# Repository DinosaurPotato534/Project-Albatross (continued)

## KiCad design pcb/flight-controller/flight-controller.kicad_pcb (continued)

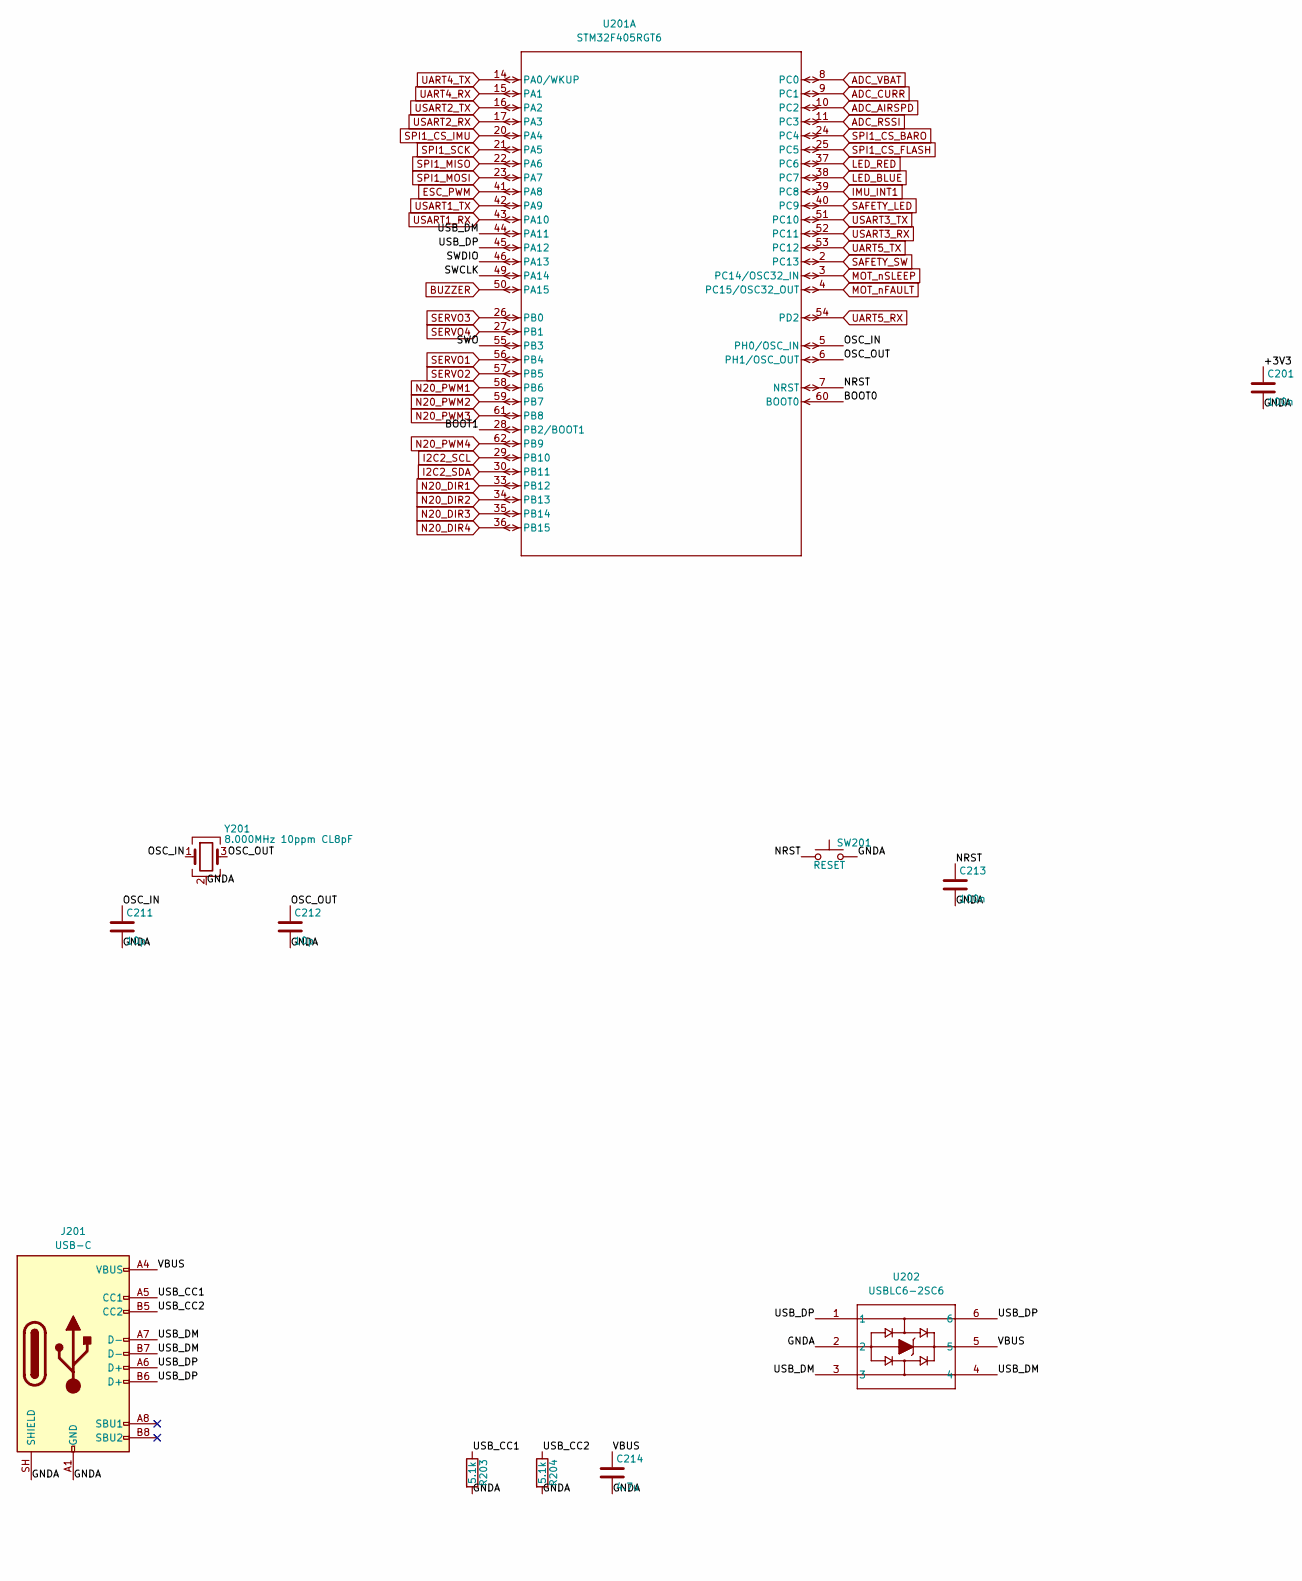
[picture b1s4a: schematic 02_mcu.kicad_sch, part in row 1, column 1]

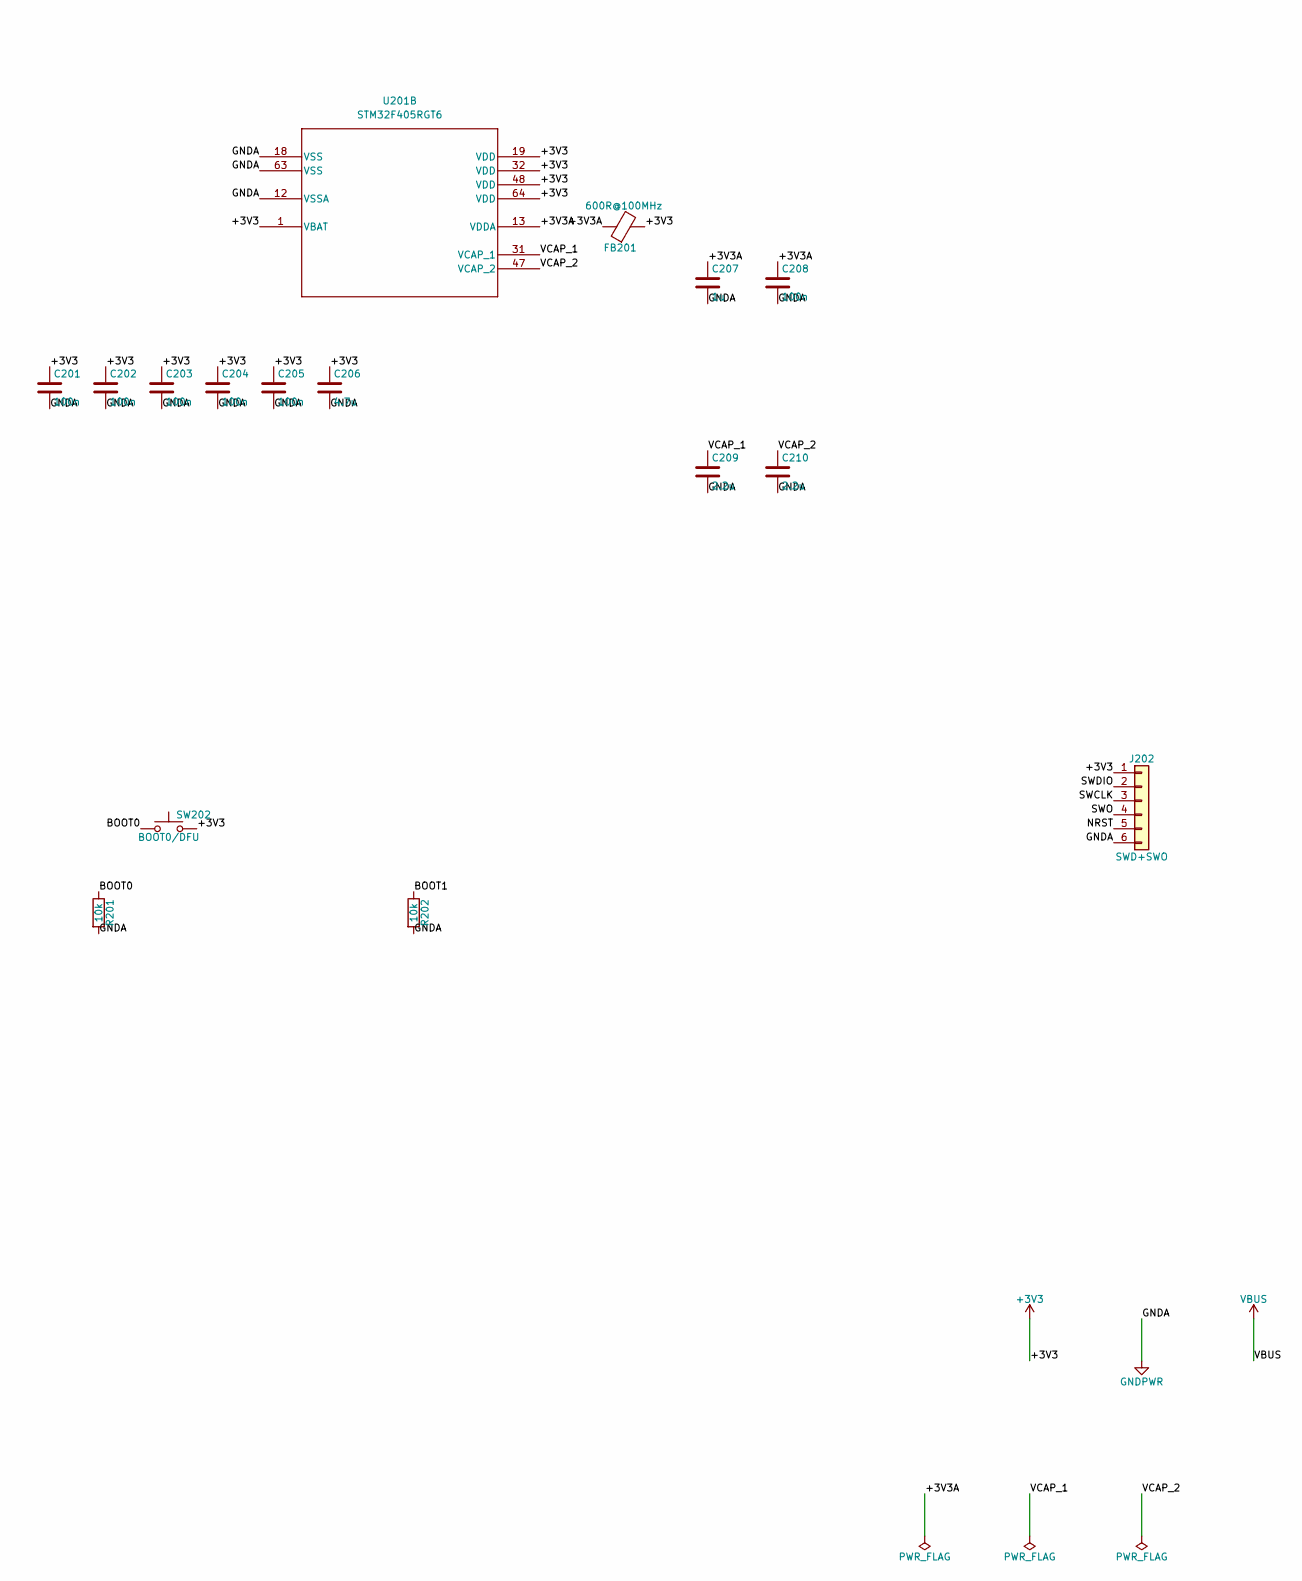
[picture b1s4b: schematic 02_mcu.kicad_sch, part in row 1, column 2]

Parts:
C201, C202, C203, C204, C205, C208, C213: 100n; C_0402_1005Metric
C206, C214: 4.7u; C_0805_2012Metric
C207: 1u; C_0603_1608Metric
C209, C210: 2.2u; C_0603_1608Metric
C211, C212: 10p; C_0402_1005Metric
FB201: 600R@100MHz; L_0805_2012Metric
J201: USB-C; USB_C_Receptacle_GCT_USB4085
J202: SWD+SWO; PinHeader_1x06_P1.27mm_Vertical
R201, R202: 10k; R_0603_1608Metric
R203, R204: 5.1k; R_0402_1005Metric
SW201: RESET; SW_SPST_B3S-1000
SW202: BOOT0/DFU; SW_SPST_B3S-1000
U201: STM32F405RGT6; LQFP64-10x10mm
U202: USBLC6-2SC6; SOT23-6L_STM
Y201: 8.000MHz 10ppm CL8pF; Crystal_SMD_3225-4Pin_3.2x2.5mm

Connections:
/02_MCU/BOOT0: R201.1, SW202.1, U201.60 (BOOT0)
/02_MCU/BOOT1: R202.1, U201.28 (PB2/BOOT1)
/02_MCU/NRST: C213.1, J202.5, SW201.1, U201.7 (NRST)
/02_MCU/OSC_IN: C211.1, U201.5 (PH0/OSC_IN), Y201.1
/02_MCU/OSC_OUT: C212.1, U201.6 (PH1/OSC_OUT), Y201.3
/02_MCU/SWCLK: J202.3, U201.49 (PA14)
/02_MCU/SWDIO: J202.2, U201.46 (PA13)
/02_MCU/SWO: J202.4, U201.55 (PB3)
/02_MCU/USB_CC1: J201.A5 (CC1), R203.1
/02_MCU/USB_CC2: J201.B5 (CC2), R204.1
/02_MCU/USB_DM: J201.A7 (D-), J201.B7 (D-), U201.44 (PA11), U202.3, U202.4
/02_MCU/USB_DP: J201.A6 (D+), J201.B6 (D+), U201.45 (PA12), U202.1, U202.6
ADC_AIRSPD: U201.10 (PC2); also elsewhere on the board
ADC_CURR: U201.9 (PC1); also elsewhere on the board
ADC_RSSI: U201.11 (PC3); also elsewhere on the board
ADC_VBAT: U201.8 (PC0); also elsewhere on the board
BUZZER: U201.50 (PA15); also elsewhere on the board
ESC_PWM: U201.41 (PA8); also elsewhere on the board
I2C2_SCL: U201.29 (PB10); also elsewhere on the board
I2C2_SDA: U201.30 (PB11); also elsewhere on the board
IMU_INT1: U201.39 (PC8); also elsewhere on the board
LED_BLUE: U201.38 (PC7); also elsewhere on the board
LED_RED: U201.37 (PC6); also elsewhere on the board
MOT_nFAULT: U201.4 (PC15/OSC32_OUT); also elsewhere on the board
MOT_nSLEEP: U201.3 (PC14/OSC32_IN); also elsewhere on the board
N20_DIR1: U201.33 (PB12); also elsewhere on the board
N20_DIR2: U201.34 (PB13); also elsewhere on the board
N20_DIR3: U201.35 (PB14); also elsewhere on the board
N20_DIR4: U201.36 (PB15); also elsewhere on the board
N20_PWM1: U201.58 (PB6); also elsewhere on the board
N20_PWM2: U201.59 (PB7); also elsewhere on the board
N20_PWM3: U201.61 (PB8); also elsewhere on the board
N20_PWM4: U201.62 (PB9); also elsewhere on the board
SAFETY_LED: U201.40 (PC9); also elsewhere on the board
SAFETY_SW: U201.2 (PC13); also elsewhere on the board
SERVO1: U201.56 (PB4); also elsewhere on the board
SERVO2: U201.57 (PB5); also elsewhere on the board
SERVO3: U201.26 (PB0); also elsewhere on the board
SERVO4: U201.27 (PB1); also elsewhere on the board
SPI1_CS_BARO: U201.24 (PC4); also elsewhere on the board
SPI1_CS_FLASH: U201.25 (PC5); also elsewhere on the board
SPI1_CS_IMU: U201.20 (PA4); also elsewhere on the board
SPI1_MISO: U201.22 (PA6); also elsewhere on the board
SPI1_MOSI: U201.23 (PA7); also elsewhere on the board
SPI1_SCK: U201.21 (PA5); also elsewhere on the board
UART4_RX: U201.15 (PA1); also elsewhere on the board
UART4_TX: U201.14 (PA0/WKUP); also elsewhere on the board
UART5_RX: U201.54 (PD2); also elsewhere on the board
UART5_TX: U201.53 (PC12); also elsewhere on the board
USART1_RX: U201.43 (PA10); also elsewhere on the board
USART1_TX: U201.42 (PA9); also elsewhere on the board
USART2_RX: U201.17 (PA3); also elsewhere on the board
USART2_TX: U201.16 (PA2); also elsewhere on the board
USART3_RX: U201.52 (PC11); also elsewhere on the board
USART3_TX: U201.51 (PC10); also elsewhere on the board

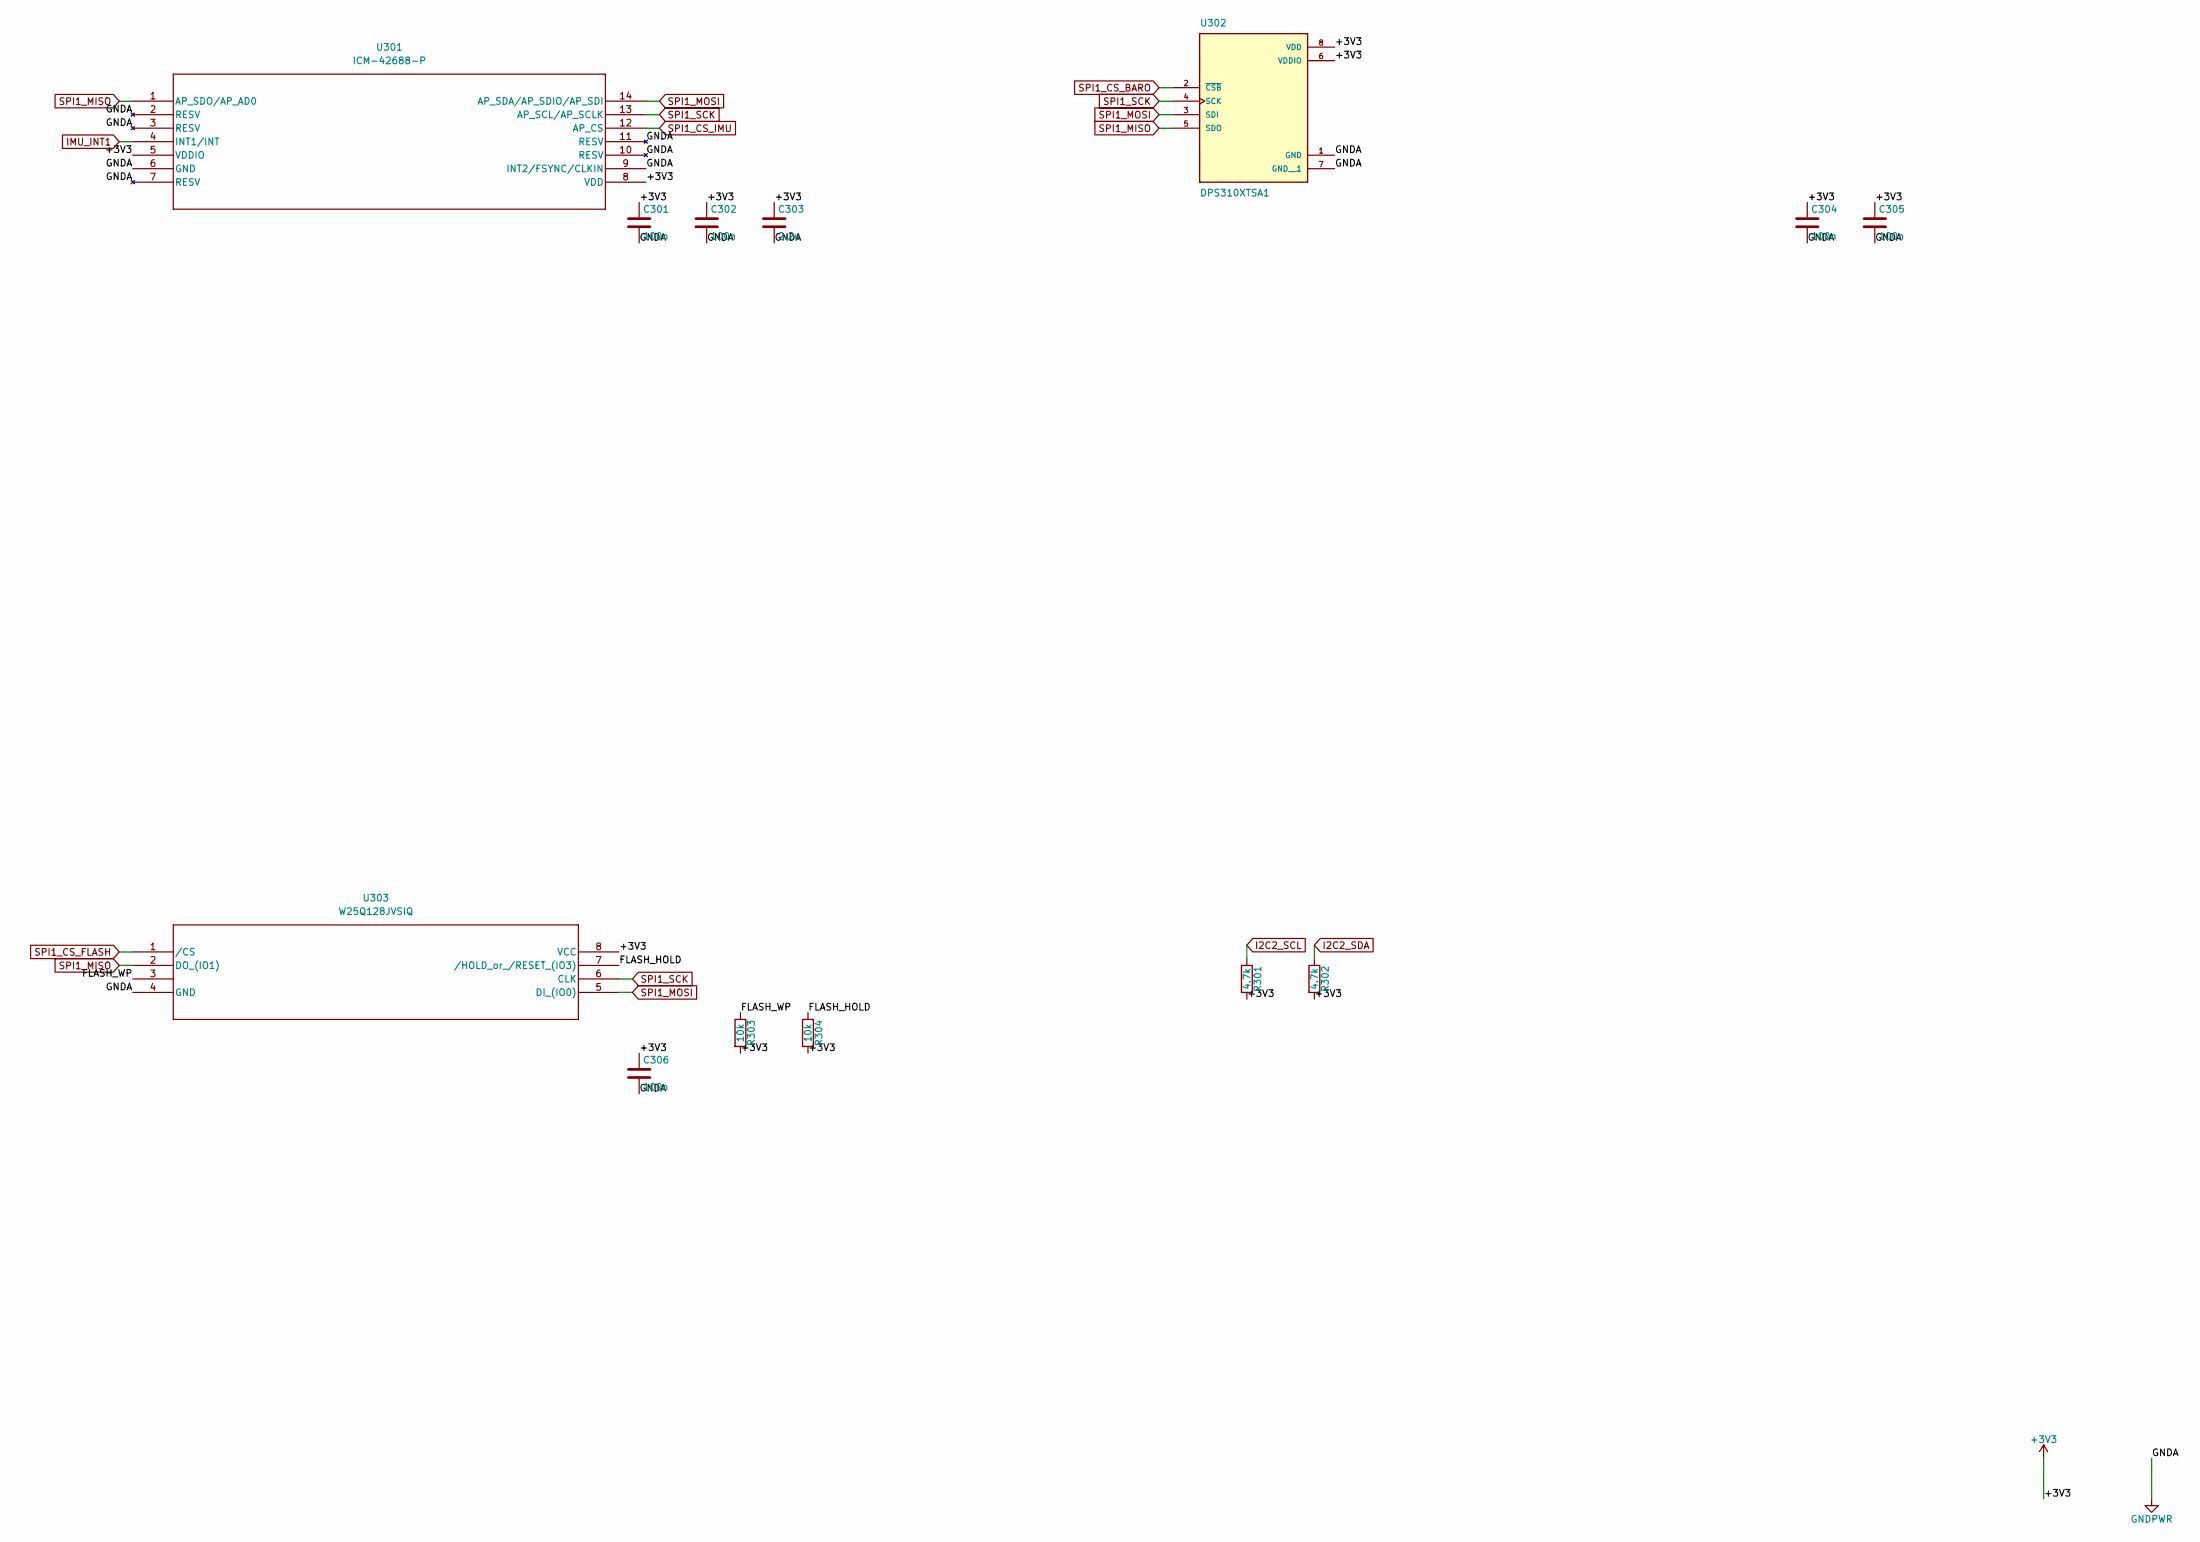
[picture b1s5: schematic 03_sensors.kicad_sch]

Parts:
C301, C302, C304, C305, C306: 100n; C_0402_1005Metric
C303: 2.2u; C_0603_1608Metric
R301, R302: 4.7k; R_0603_1608Metric
R303, R304: 10k; R_0402_1005Metric
U301: ICM-42688-P; LGA14_2P5X3X0P91_TDK
U302: DPS310XTSA1; XDCR_DPS310XTSA1
U303: W25Q128JVSIQ; SOIC_128JVSIQ_WIN

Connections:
/03_SENSORS/FLASH_HOLD: R304.1, U303.7 (/HOLD_or_/RESET_(IO3))
/03_SENSORS/FLASH_WP: R303.1, U303.3
I2C2_SCL: R301.1; also elsewhere on the board
I2C2_SDA: R302.1; also elsewhere on the board
IMU_INT1: U301.4 (INT1/INT); also elsewhere on the board
SPI1_CS_BARO: U302.2 (~CSB); also elsewhere on the board
SPI1_CS_FLASH: U303.1 (/CS); also elsewhere on the board
SPI1_CS_IMU: U301.12 (AP_CS); also elsewhere on the board
SPI1_MISO: U301.1 (AP_SDO/AP_AD0), U302.5 (SDO), U303.2 (DO_(IO1)); also elsewhere on the board
SPI1_MOSI: U301.14 (AP_SDA/AP_SDIO/AP_SDI), U302.3 (SDI), U303.5 (DI_(IO0)); also elsewhere on the board
SPI1_SCK: U301.13 (AP_SCL/AP_SCLK), U302.4 (SCK), U303.6 (CLK); also elsewhere on the board

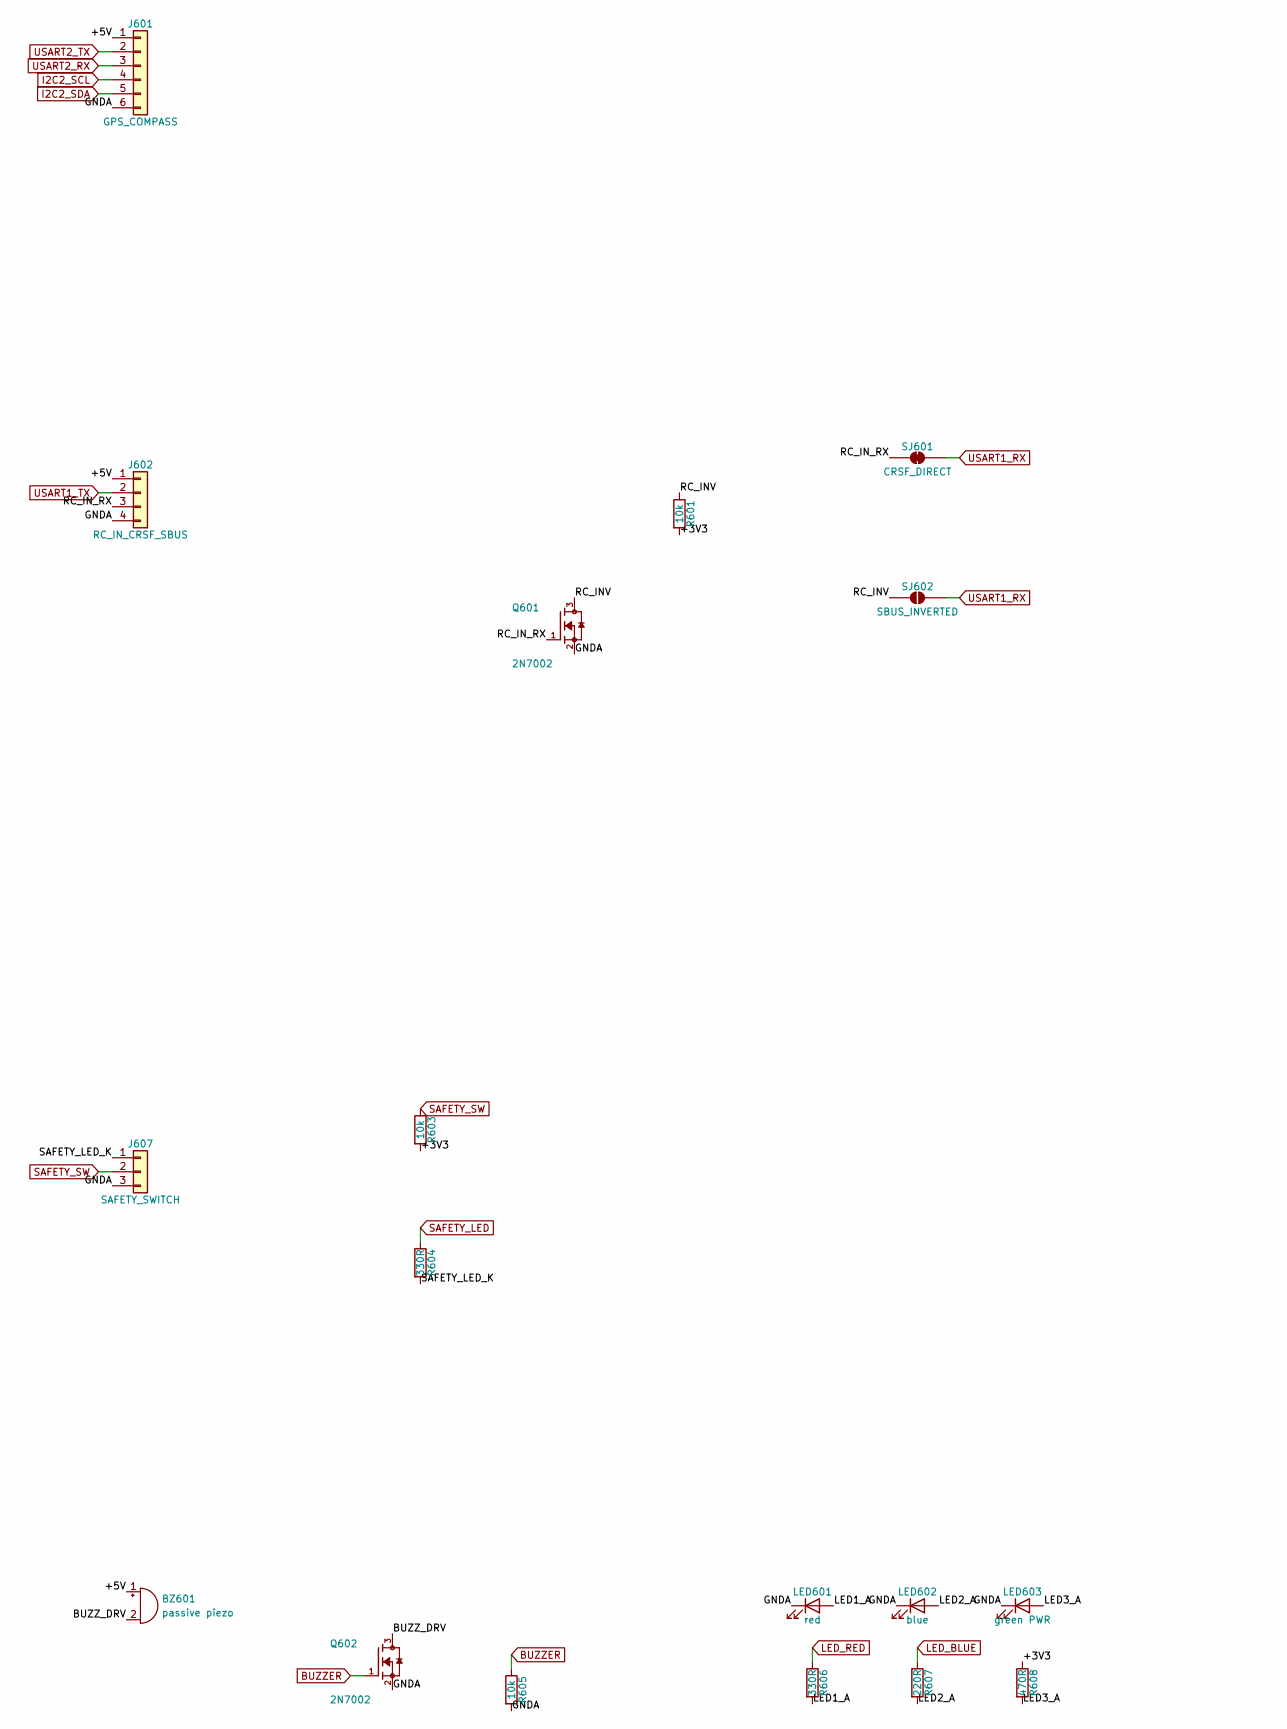
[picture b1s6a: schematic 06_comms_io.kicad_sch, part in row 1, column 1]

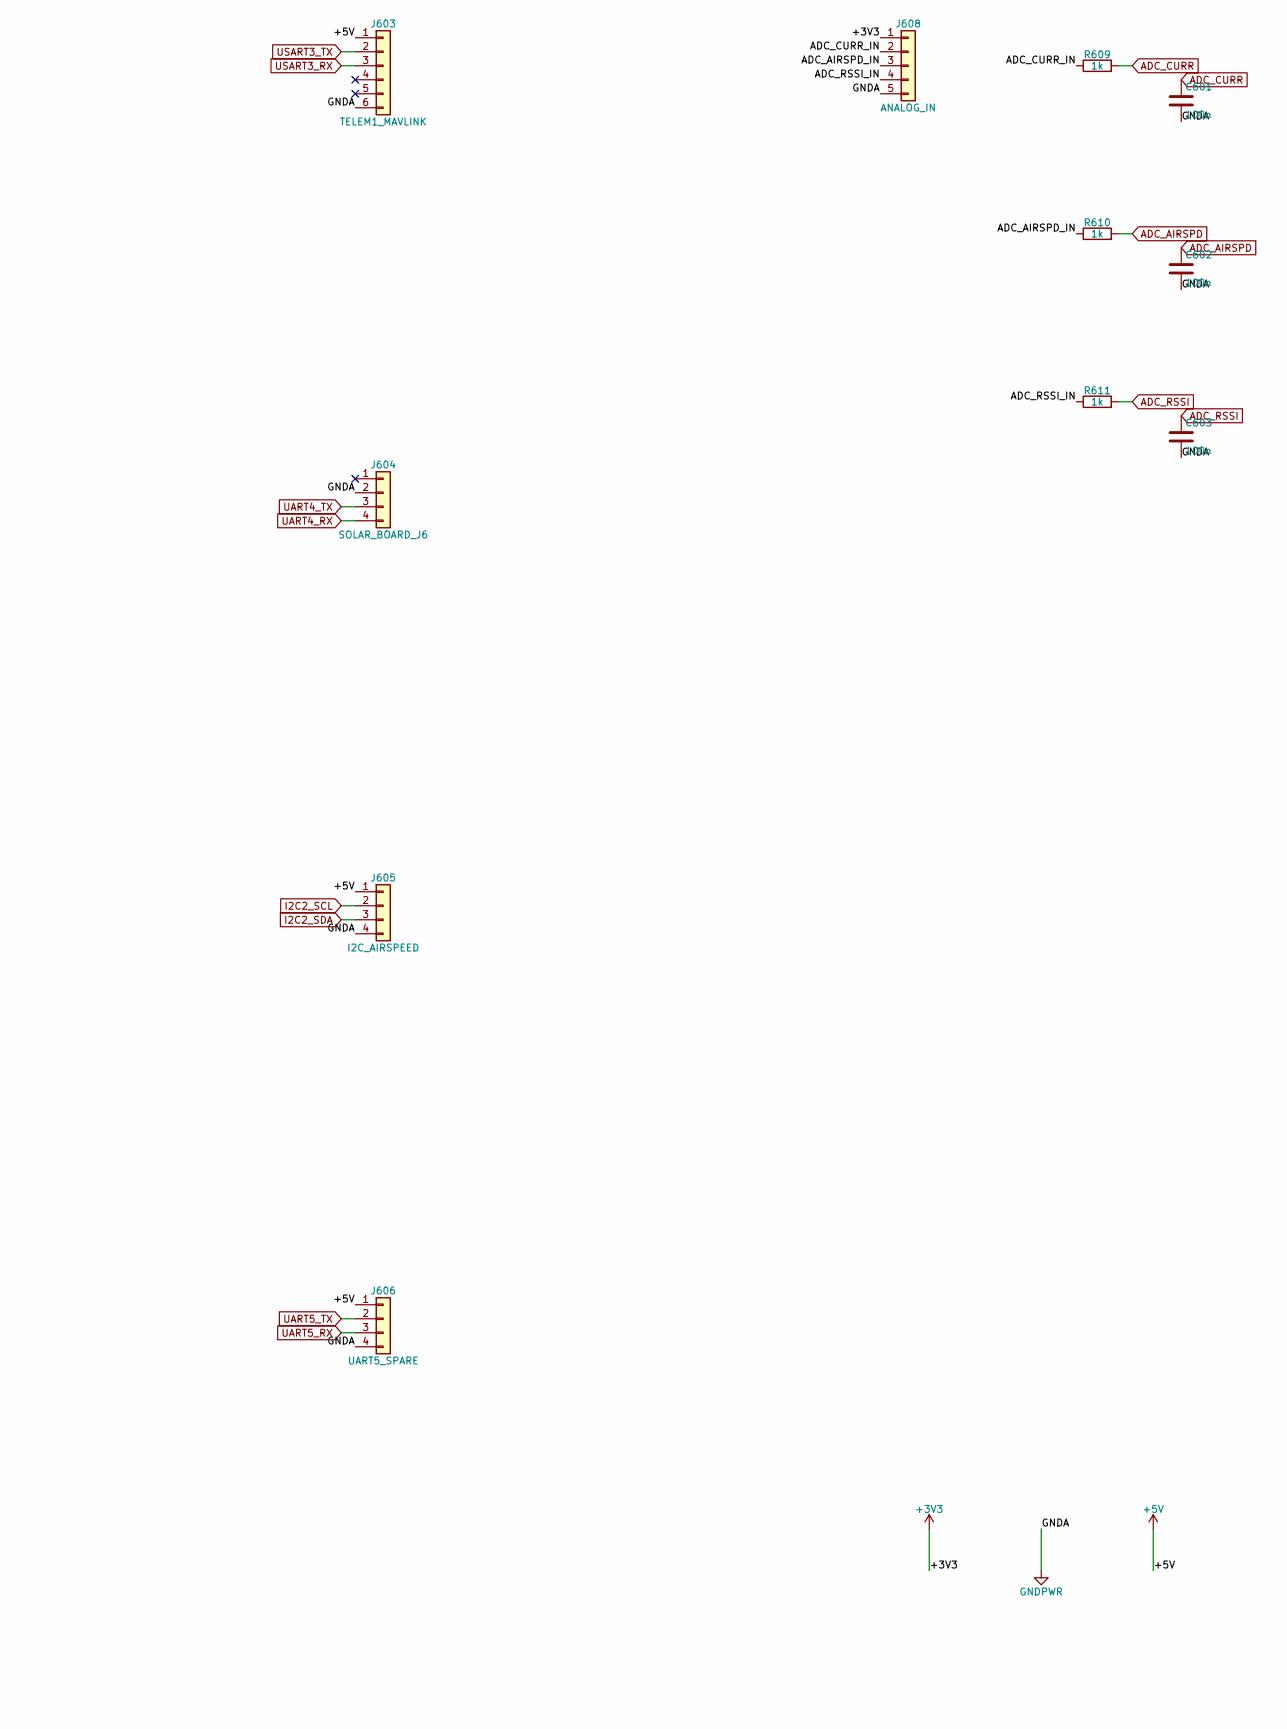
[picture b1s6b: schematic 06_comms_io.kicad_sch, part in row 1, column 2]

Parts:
BZ601: passive piezo; Buzzer_12x9.5RM7.6
C601, C602, C603: 100n; C_0603_1608Metric
J601: GPS_COMPASS; JST_GH_BM06B-GHS-TBT_1x06-1MP_P1.25mm_Vertical
J602: RC_IN_CRSF_SBUS; JST_GH_BM04B-GHS-TBT_1x04-1MP_P1.25mm_Vertical
J603: TELEM1_MAVLINK; JST_GH_BM06B-GHS-TBT_1x06-1MP_P1.25mm_Vertical
J604: SOLAR_BOARD_J6; JST_GH_BM04B-GHS-TBT_1x04-1MP_P1.25mm_Vertical
J605: I2C_AIRSPEED; JST_GH_BM04B-GHS-TBT_1x04-1MP_P1.25mm_Vertical
J606: UART5_SPARE; JST_GH_BM04B-GHS-TBT_1x04-1MP_P1.25mm_Vertical
J607: SAFETY_SWITCH; JST_GH_BM03B-GHS-TBT_1x03-1MP_P1.25mm_Vertical
J608: ANALOG_IN; JST_GH_BM05B-GHS-TBT_1x05-1MP_P1.25mm_Vertical
LED601: red; LED_0603_1608Metric
LED602: blue; LED_0603_1608Metric
LED603: green PWR; LED_0603_1608Metric
Q601, Q602: 2N7002; TRANS_2N7002
R601, R603, R605: 10k; R_0603_1608Metric
R604, R606: 330R; R_0603_1608Metric
R607: 220R; R_0603_1608Metric
R608: 470R; R_0603_1608Metric
R609, R610, R611: 1k; R_0603_1608Metric
SJ601: CRSF_DIRECT; SolderJumper-2_P1.3mm_Bridged_Pad1.0x1.5mm
SJ602: SBUS_INVERTED; SolderJumper-2_P1.3mm_Open_Pad1.0x1.5mm

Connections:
/06_COMMS_IO/ADC_AIRSPD_IN: J608.3, R610.1
/06_COMMS_IO/ADC_CURR_IN: J608.2, R609.1
/06_COMMS_IO/ADC_RSSI_IN: J608.4, R611.1
/06_COMMS_IO/BUZZ_DRV: BZ601.2 (-), Q602.3
/06_COMMS_IO/LED1_A: LED601.2 (A), R606.2
/06_COMMS_IO/LED2_A: LED602.2 (A), R607.2
/06_COMMS_IO/LED3_A: LED603.2 (A), R608.2
/06_COMMS_IO/RC_INV: Q601.3, R601.1, SJ602.1 (A)
/06_COMMS_IO/RC_IN_RX: J602.3, Q601.1, SJ601.1 (A)
/06_COMMS_IO/SAFETY_LED_K: J607.1, R604.2
ADC_AIRSPD: C602.1, R610.2; also elsewhere on the board
ADC_CURR: C601.1, R609.2; also elsewhere on the board
ADC_RSSI: C603.1, R611.2; also elsewhere on the board
BUZZER: Q602.1, R605.1; also elsewhere on the board
I2C2_SCL: J601.4, J605.2; also elsewhere on the board
I2C2_SDA: J601.5, J605.3; also elsewhere on the board
LED_BLUE: R607.1; also elsewhere on the board
LED_RED: R606.1; also elsewhere on the board
SAFETY_LED: R604.1; also elsewhere on the board
SAFETY_SW: J607.2, R603.1; also elsewhere on the board
UART4_RX: J604.4; also elsewhere on the board
UART4_TX: J604.3; also elsewhere on the board
UART5_RX: J606.3; also elsewhere on the board
UART5_TX: J606.2; also elsewhere on the board
USART1_RX: SJ601.2 (B), SJ602.2 (B); also elsewhere on the board
USART1_TX: J602.2; also elsewhere on the board
USART2_RX: J601.3; also elsewhere on the board
USART2_TX: J601.2; also elsewhere on the board
USART3_RX: J603.3; also elsewhere on the board
USART3_TX: J603.2; also elsewhere on the board

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
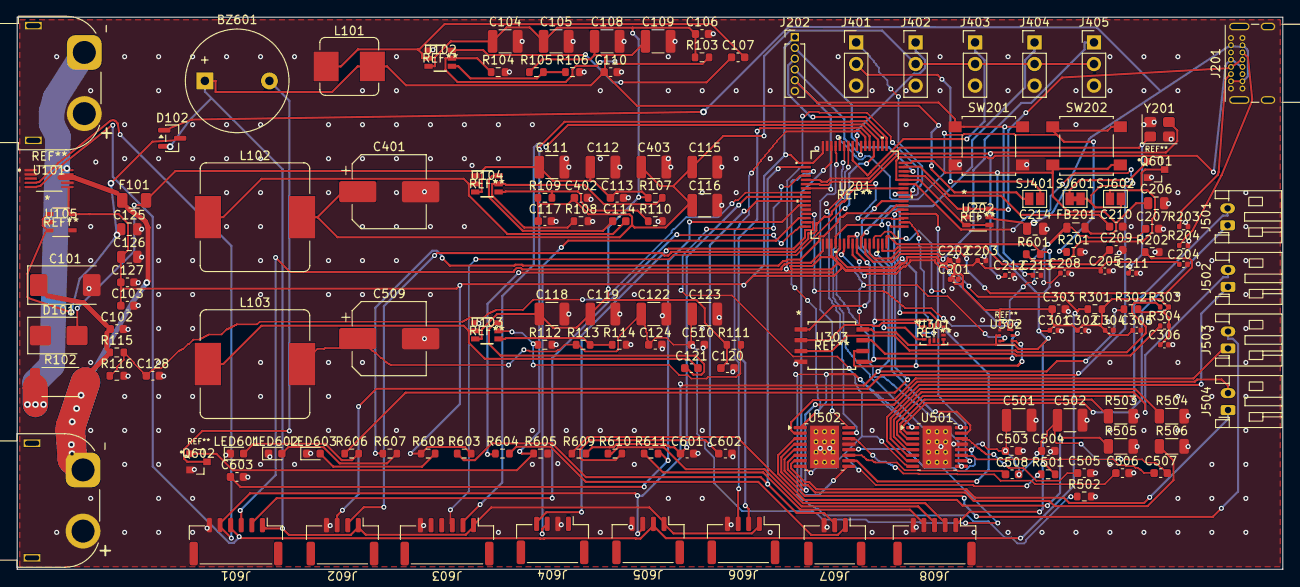
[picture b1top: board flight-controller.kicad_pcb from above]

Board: 2 copper layers, 149.0 x 65.0 mm, 155 parts (0 on the bottom side), 109 nets.
